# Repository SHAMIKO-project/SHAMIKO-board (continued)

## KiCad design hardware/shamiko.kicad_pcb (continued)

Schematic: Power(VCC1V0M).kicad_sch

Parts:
C27: 100u; CP_Elec_6.3x7.7; LCSC C48587228
C28, C35: 10u; C_0805_2012Metric; LCSC C440198
C29, C36: 330u; CP_Elec_6.3x7.7; LCSC C48587229
C30: 47u; C_0805_2012Metric; LCSC C124129
C31, C37: 0.01u; C_0603_1608Metric; LCSC C85973
C32: 0.1u; C_0603_1608Metric; LCSC C77055
C33: 2.2u; C_0805_2012Metric; LCSC C117966
C34: 4.7u; C_0805_2012Metric; LCSC C408144
C38: 1u; C_0603_1608Metric; LCSC C77386
C39: 1n; C_0603_1608Metric; LCSC C77026
IC1: LT3071; LT3071EUFD#PBF; LCSC C117304
J2, J3: SMA; SMA_Amphenol_132134-14_Vertical; LCSC C3174425
JP1: Jumper_2_Open; PinHeader_1x02_P2.54mm_Vertical; LCSC C42431798
R13: 0; R_2512_6332Metric_Pad1.40x3.35mm_HandSolder; LCSC C5204052
R14: 50k; R_0603_1608Metric; LCSC C861451
R15: 0; R_2512_6332Metric; LCSC C5204052; not fitted
R16: 100m; R_2512_6332Metric_Pad1.40x3.35mm_HandSolder; LCSC C840616
R17, R18: 0; R_1206_3216Metric; LCSC C137394
R19: 1k; R_0603_1608Metric; LCSC C22548
RV1: 10k; Potentiometer_Bourns_3296W_Vertical; LCSC C34846
TP1: TestPoint; TestPoint_Pad_D1.0mm; LCSC None; not fitted

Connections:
+1V0M: JP1.2 (B), R15.2, R16.2, R18.1, TP1.1; also elsewhere on the board
+1V0MB: R13.2, R15.1; also elsewhere on the board
+1V2: C29.1, C30.1, IC1.5 (IN_1), IC1.6 (IN_2), IC1.7 (IN_3), IC1.8 (IN_4), RV1.1; also elsewhere on the board
+3.3VP: C27.1, C28.1, IC1.27 (BIAS), IC1.28 (EN), R14.1; also elsewhere on the board
GND: C27.2, C28.2, C29.2, C30.2, C31.2, C32.2, C33.2, C34.2, C35.2, C36.2, C37.2, C38.2, C39.2, IC1.4 (GND_1), IC1.9 (GND_2), IC1.10 (GND_3), IC1.11 (GND_4), IC1.12 (GND_5), IC1.13 (GND_6), IC1.14 (GND_7), IC1.20 (GND_8), IC1.25 (VO2), IC1.26 (GND_9), IC1.29 (GND_10), J2.2 (Ext), J3.2 (Ext), R19.2, RV1.3; also elsewhere on the board
unnamed: IC1.21 (IMON), R19.1
unnamed: C38.1, IC1.22 (MARGA), RV1.2
unnamed: C31.1, C32.1, C33.1, C34.1, C35.1, C36.1, IC1.15 (OUT_1), IC1.16 (OUT_2), IC1.17 (OUT_3), IC1.18 (OUT_4), IC1.19 (SENSE), JP1.1 (A), R13.1, R16.1, R17.1
unnamed: IC1.2 (PWRGD), R14.2
unnamed: C37.1, IC1.3 (REF/BYP)
unnamed: C39.1, IC1.1 (VIOC)
unnamed: J2.1 (In), R17.2
unnamed: J3.1 (In), R18.2

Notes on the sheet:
NMT

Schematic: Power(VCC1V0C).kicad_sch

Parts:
C40, C42: 100u; CP_Elec_6.3x7.7; LCSC C48587228
C41, C43, C46: 10u; C_0805_2012Metric; LCSC C440198
C44: 2.2u; C_0603_1608Metric; LCSC C77047
C45: 4.7u; C_0603_1608Metric; LCSC C90057
C47: 330u; CP_Elec_6.3x7.7; LCSC C48587229
C48: 0.01u; C_0603_1608Metric; LCSC C85973
C49: 1u; C_0603_1608Metric; LCSC C77386
C50: 1n; C_0603_1608Metric; LCSC C77026
IC2: LT3071; LT3071EUFD#PBF; LCSC C117304
R20: 50k; R_0603_1608Metric; LCSC C861451
R21: 1k; R_0603_1608Metric; LCSC C22548
RV2: 10k; Potentiometer_Bourns_3296W_Vertical; LCSC C34846
TP2: TestPoint; TestPoint_Pad_D1.0mm; LCSC None; not fitted

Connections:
+1V0C: C44.1, C45.1, C46.1, C47.1, IC2.15 (OUT_1), IC2.16 (OUT_2), IC2.17 (OUT_3), IC2.18 (OUT_4), IC2.19 (SENSE), TP2.1; also elsewhere on the board
+1V2: C42.1, C43.1, IC2.5 (IN_1), IC2.6 (IN_2), IC2.7 (IN_3), IC2.8 (IN_4), RV2.1; also elsewhere on the board
+3.3VP: C40.1, C41.1, IC2.27 (BIAS), IC2.28 (EN), R20.1; also elsewhere on the board
GND: C40.2, C41.2, C42.2, C43.2, C44.2, C45.2, C46.2, C47.2, C48.2, C49.2, C50.2, IC2.4 (GND_1), IC2.9 (GND_2), IC2.10 (GND_3), IC2.11 (GND_4), IC2.12 (GND_5), IC2.13 (GND_6), IC2.14 (GND_7), IC2.20 (GND_8), IC2.25 (VO2), IC2.26 (GND_9), IC2.29 (GND_10), R21.2, RV2.3; also elsewhere on the board
unnamed: IC2.21 (IMON), R21.1
unnamed: C49.1, IC2.22 (MARGA), RV2.2
unnamed: IC2.2 (PWRGD), R20.2
unnamed: C48.1, IC2.3 (REF/BYP)
unnamed: C50.1, IC2.1 (VIOC)

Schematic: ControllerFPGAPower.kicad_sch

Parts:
C146, C153, C160, C167, C173, C187: 47u; C_0805_2012Metric; LCSC C124129
C147, C148, C154, C155, C161, C162, C168, C169, C170, C174, C175, C182, C183, C188: 4.7u; C_0603_1608Metric; LCSC C90057
C149, C150, C151, C152, C156, C157, C158, C159, C163, C164, C165, C166, C171, C172, C176, C177, C178, C179, C180, C184, C185, C186, C189: 0.47u; C_0402_1005Metric; LCSC C77003
C181: 0.01u; C_0402_1005Metric; LCSC C15195
FB3, FB4: MMZ1005S601CT000; LCSC C76804
U5: XC7S25-1CSGA225C; LCSC C1521699

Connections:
+1V0C: C182.1, C183.1, C184.1, C185.1, C186.1, C187.1, C188.1, C189.1, U5.E8 (VCCINT_1), U5.E10 (VCCINT_2), U5.F7 (VCCINT_3), U5.G6 (VCCBRAM_1), U5.G10 (VCCINT_4), U5.H7 (VCCINT_5), U5.J6 (VCCBRAM_2), U5.J10 (VCCINT_6), U5.K7 (VCCINT_7), U5.K9 (VCCINT_8); also elsewhere on the board
+1V8: C167.1, C168.1, C169.1, C170.1, C171.1, C172.1, FB3.1, U5.L6 (VCCAUX_1), U5.L8 (VCCAUX_2); also elsewhere on the board
+3V3C: C146.1, C147.1, C148.1, C149.1, C150.1, C151.1, C152.1, C153.1, C154.1, C155.1, C156.1, C157.1, C158.1, C159.1, C160.1, C161.1, C162.1, C163.1, C164.1, C165.1, C166.1, C173.1, C174.1, C175.1, C176.1, C177.1, C178.1, C179.1, U5.B7 (VCCO_15_1), U5.C3 (VCCO_34_1), U5.C11 (VCCO_15_2), U5.E6 (VCCO_0_1), U5.F12 (VCCO_15_3), U5.G2 (VCCO_34_2), U5.H5 (CFGBVS_0), U5.J14 (VCCO_14_1), U5.L3 (VCCO_34_3), U5.M12 (VCCO_14_2), U5.P5 (VCCO_0_2), U5.P9 (VCCO_14_3); also elsewhere on the board
GND: C146.2, C147.2, C148.2, C149.2, C150.2, C151.2, C152.2, C153.2, C154.2, C155.2, C156.2, C157.2, C158.2, C159.2, C160.2, C161.2, C162.2, C163.2, C164.2, C165.2, C166.2, C167.2, C168.2, C169.2, C170.2, C171.2, C172.2, C173.2, C174.2, C175.2, C176.2, C177.2, C178.2, C179.2, C180.2, C182.2, C183.2, C184.2, C185.2, C186.2, C187.2, C188.2, C189.2, FB4.1, U5.A1 (GND_1), U5.A15 (GND_2), U5.B8 (GND_3), U5.C2 (GND_4), U5.C12 (GND_5), U5.D5 (VCCBATT_0), U5.D6 (GND_6), U5.D14 (GND_7), U5.E4 (GND_8), U5.E7 (GND_9), U5.E9 (GND_10), U5.F6 (GND_11), U5.F10 (GND_12), U5.F13 (GND_13), U5.G3 (GND_14), U5.G7 (GND_15), U5.H6 (GND_16), U5.H10 (GND_17), U5.J7 (GND_18), U5.J8 (DXN_0), U5.J9 (DXP_0), U5.J13 (GND_19), U5.K6 (GND_20), U5.K8 (GND_21), U5.K10 (GND_22), U5.L2 (GND_23), U5.L7 (GND_24), U5.L9 (GND_25), U5.M11 (GND_26), U5.P4 (GND_27), U5.P8 (GND_28), U5.P13 (GND_29), U5.R1 (GND_30), U5.R15 (GND_31); also elsewhere on the board
unnamed: C181.2, FB4.2, U5.F8 (GNDADC_0), U5.G8 (VREFN_0), U5.G9 (VP_0), U5.H8 (VN_0), U5.H9 (VREFP_0)
unnamed: C180.1, C181.1, FB3.2, U5.F9 (VCCADC_0)

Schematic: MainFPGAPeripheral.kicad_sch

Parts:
D8, D9, D10, D11, D12, D13, D14, D15: R_LED; LED_0603_1608Metric; LCSC C965798
R65, R66, R67, R68, R69, R70, R71, R72: 200; R_0603_1608Metric; LCSC C2907123
RN1, RN2, RN3: 4.7k; YAGEO_R_network; LCSC C327044
SW3, SW4, SW5, SW6: SW_MEC_5E; MySW_PUSH_6mm_H5mm; LCSC C393938
SW7: SW_DIP_x08; SW_DIP_SPSTx08_Slide_9.78x22.5mm_W8.61mm_P2.54mm; LCSC C2842674

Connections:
+3V3M: R65.1, R66.1, R67.1, R68.1, R69.1, R70.1, R71.1, R72.1, SW3.3 (K), SW3.4 (A), SW4.3 (K), SW4.4 (A), SW5.3 (K), SW5.4 (A), SW6.3 (K), SW6.4 (A), SW7.9, SW7.10, SW7.11, SW7.12, SW7.13, SW7.14, SW7.15, SW7.16; also elsewhere on the board
GND: RN1.1, RN1.2, RN1.3, RN1.4, RN2.1, RN2.2, RN2.3, RN2.4, RN3.1, RN3.2, RN3.3, RN3.4; also elsewhere on the board
M_DIPSW_0: RN3.5, SW7.8; also elsewhere on the board
M_DIPSW_1: RN3.6, SW7.7; also elsewhere on the board
M_DIPSW_2: RN3.7, SW7.6; also elsewhere on the board
M_DIPSW_3: RN3.8, SW7.5; also elsewhere on the board
M_DIPSW_4: RN2.5, SW7.4; also elsewhere on the board
M_DIPSW_5: RN2.6, SW7.3; also elsewhere on the board
M_DIPSW_6: RN2.7, SW7.2; also elsewhere on the board
M_DIPSW_7: RN2.8, SW7.1; also elsewhere on the board
M_LED_0: D8.1 (K); also elsewhere on the board
M_LED_1: D9.1 (K); also elsewhere on the board
M_LED_2: D10.1 (K); also elsewhere on the board
M_LED_3: D11.1 (K); also elsewhere on the board
M_LED_4: D12.1 (K); also elsewhere on the board
M_LED_5: D13.1 (K); also elsewhere on the board
M_LED_6: D14.1 (K); also elsewhere on the board
M_LED_7: D15.1 (K); also elsewhere on the board
M_TACTSW_0: RN1.5, SW6.1, SW6.2; also elsewhere on the board
M_TACTSW_1: RN1.6, SW5.1, SW5.2; also elsewhere on the board
M_TACTSW_2: RN1.7, SW4.1, SW4.2; also elsewhere on the board
M_TACTSW_3: RN1.8, SW3.1, SW3.2; also elsewhere on the board
unnamed: D8.2 (A), R65.2
unnamed: D9.2 (A), R66.2
unnamed: D10.2 (A), R67.2
unnamed: D11.2 (A), R68.2
unnamed: D12.2 (A), R69.2
unnamed: D13.2 (A), R70.2
unnamed: D14.2 (A), R71.2
unnamed: D15.2 (A), R72.2

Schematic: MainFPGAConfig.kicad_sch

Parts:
C190, C191, C192: 0.1u; C_0603_1608Metric; LCSC C77055
D2: B_LED; LED_0603_1608Metric; LCSC C19171394
D3, D4: G_LED; LED_0603_1608Metric; LCSC C5342733
J4: JTAG_CONFIG; JTAG_2x7_P2.54mm; LCSC C240854
R31, R32, R33, R40, R41, R43, R44, R45: 4.7k; R_0603_1608Metric; LCSC C99782
R34, R35, R36, R47: 1k; R_0603_1608Metric; LCSC C22548
R37, R38, R39: 200; R_0603_1608Metric; LCSC C2907123
R42: 2.4k; R_0603_1608Metric; LCSC C22940
R46: 330; R_0603_1608Metric; LCSC C105881
SW1: SW_DIP_x03; SW_DIP_SPSTx03_Slide_9.78x9.8mm_W8.61mm_P2.54mm; LCSC C3012353
U4: XC7S100-2FGGA484I; Xilinx_FBG484; LCSC C1521770
U6: IS25LP064A-JLLE; WSON-8-1EP_8x6mm_P1.27mm_EP3.4x4.3mm; LCSC C1349830
U7, U8: SN74LVC2G17DCKRE4; LCSC C50714

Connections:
+3V3M: C190.1, C191.1, C192.1, D3.2 (A), D4.2 (A), J4.2, R31.1, R32.1, R33.1, R40.1, R41.1, R42.1, R43.1, R44.1, R45.1, R46.1, SW1.1, SW1.2, SW1.3, U6.8 (VCC), U7.5 (VCC), U8.5 (VCC); also elsewhere on the board
/Main FPGA Configuration/MX_JTAG_TCK: U4.G9 (TCK_0), U7.4 (2Y)
/Main FPGA Configuration/MX_JTAG_TDI: U4.W9 (TDI_0), U8.4 (2Y)
/Main FPGA Configuration/MX_JTAG_TDO: R43.2, U4.W10 (TDO_0), U8.1 (1A)
/Main FPGA Configuration/MX_JTAG_TMS: U4.Y10 (TMS_0), U7.6 (1Y)
/Main FPGA Configuration/M_CONFIG_M0: R34.1, SW1.6, U4.T11 (M0_0)
/Main FPGA Configuration/M_CONFIG_M1: R35.1, SW1.5, U4.T10 (M1_0)
/Main FPGA Configuration/M_CONFIG_M2: R36.1, SW1.4, U4.U10 (M2_0)
/Main FPGA Configuration/M_JTAG_TCK: J4.6, R32.2, U7.3 (2A)
/Main FPGA Configuration/M_JTAG_TDI: J4.10, R33.2, U8.3 (2A)
/Main FPGA Configuration/M_JTAG_TDO: J4.8, U8.6 (1Y)
/Main FPGA Configuration/M_JTAG_TMS: J4.4, R31.2, U7.1 (1A)
/Main FPGA Configuration/M_S_CLOCK: U4.D9 (CCLK_0), U6.6 (SCK)
/Main FPGA Configuration/M_S_D0: U4.M21 (IO_L1P_T0_D00_MOSI_14), U6.5 (SI_(IO0))
/Main FPGA Configuration/M_S_D1: U4.M22 (IO_L1N_T0_D01_DIN_14), U6.2 (SO_(IO1))
/Main FPGA Configuration/M_S_D2: R41.2, U4.N21 (IO_L2P_T0_D02_14), U6.3 (WP#_(IO2))
/Main FPGA Configuration/M_S_D3: R40.2, U4.N22 (IO_L2N_T0_D03_14), U6.7 (HOLD#_(IO3))
/Main FPGA Configuration/M_S_SELECTn: R42.2, U4.N17 (IO_L6P_T0_FCS_B_14), U6.1 (CE#)
GND: C190.2, C191.2, C192.2, J4.1, J4.3, J4.5, J4.7, J4.9, J4.11, J4.13, R34.2, R35.2, R36.2, R37.2, R47.2, U6.4 (GND), U6.9 (EPAD), U7.2 (GND), U8.2 (GND); also elsewhere on the board
M_DONE: D2.2 (A), R46.2, U4.U9 (DONE_0); also elsewhere on the board
M_INIT_B: R38.2, R45.2, U4.T9 (INIT_B_0)
M_PROG_B: R39.2, R44.2, U4.U11 (PROGRAM_B_0); also elsewhere on the board
unnamed: D2.1 (K), R37.1
unnamed: D3.1 (K), R38.1
unnamed: D4.1 (K), R39.1
unnamed: R47.1, U4.M19 (IO_L3P_T0_DQS_PUDC_B_14)

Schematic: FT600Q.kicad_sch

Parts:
C223, C224, C225, C226, C228, C231, C232, C233, C234, C235, C236, C237, C239, C240, C241, C242: 0.1u; C_0603_1608Metric; LCSC C77055
C227: 100u; CP_Elec_6.3x7.7; LCSC C48587228
C229: 10u; C_0805_2012Metric; LCSC C440198
C230: 1u; NFM31HK103R1H3L; LCSC C92518
C238: 4.7u; C_0603_1608Metric; LCSC C90057
C243, C244: 18p; C_0603_1608Metric; LCSC C1647
FB9, FB10, FB11, FB12, FB13: BLM18PG221SN1D; BLM18SP221SN1B; LCSC C80165
FL2, FL3, FL4: DLM0NSN500HY2D; LCSC C1857796
J8: 692221030100; LCSC C5334230
R93: 4.7k; R_0603_1608Metric; LCSC C99782
R94: 10k; R_0603_1608Metric; LCSC C95204
R95: 1.6k; R_0603_1608Metric; LCSC C22847
U14: LM2937IMP-3.3; SOT-223; LCSC C140265
U15, U17, U18: TPD2EUSB30; Texas_DRT-3; LCSC C97502
U16: FT600; QFN-56-1EP_7x7mm_P0.4mm_EP4x4mm; LCSC C5252722
Y2: 30MHz; Crystal_SMD_5032-2Pin_5.0x3.2mm; LCSC C19272757

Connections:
+5V: C228.1, U14.1 (VI); also elsewhere on the board
/FT600Q/FT600_D+: FL2.1, J8.3 (D+), U15.1 (D+)
/FT600Q/FT600_D-: FL2.4, J8.2 (D-), U15.2 (D-)
/FT600Q/RID+: FL4.3, U16.28 (RIDP)
/FT600Q/RID-: FL4.2, U16.27 (RIDN)
/FT600Q/SSRX+: FL4.4, J8.9 (SSRX+), U18.1 (D+)
/FT600Q/SSRX-: FL4.1, J8.8 (SSRX-), U18.2 (D-)
/FT600Q/SSTX+: FL3.4, J8.6 (SSTX+), U17.1 (D+)
/FT600Q/SSTX-: FL3.1, J8.5 (SSTX-), U17.2 (D-)
/FT600Q/TI_C_D+: C237.1, FL3.3
/FT600Q/TI_C_D-: C236.1, FL3.2
/FT600Q/TODN: C236.2, U16.24 (TODN)
/FT600Q/TODP: C237.2, U16.25 (TODP)
/FT600Q/USB3_D+: FL2.2, U16.18 (DP)
/FT600Q/USB3_D-: FL2.3, U16.20 (DM)
/FT600Q/VD10: C238.1, C239.1, C240.1, C241.1, C242.1, U16.1 (AVDD), U16.23 (VD10), U16.26 (VD10), U16.31 (DV10), U16.37 (VD10), U16.50 (VD10)
C_RST: U16.10 (~RESET); also elsewhere on the board
FT600_BE0: U16.2 (BE_0); also elsewhere on the board
FT600_BE1: U16.3 (BE_1); also elsewhere on the board
FT600_CLK: U16.43 (CLK); also elsewhere on the board
FT600_DATA_0: U16.33 (DATA_0); also elsewhere on the board
FT600_DATA_1: U16.34 (DATA_1); also elsewhere on the board
FT600_DATA_2: U16.35 (DATA_2); also elsewhere on the board
FT600_DATA_3: U16.36 (DATA_3); also elsewhere on the board
FT600_DATA_4: U16.39 (DATA_4); also elsewhere on the board
FT600_DATA_5: U16.40 (DATA_5); also elsewhere on the board
FT600_DATA_6: U16.41 (DATA_6); also elsewhere on the board
FT600_DATA_7: U16.42 (DATA_7); also elsewhere on the board
FT600_DATA_8: U16.45 (DATA_8); also elsewhere on the board
FT600_DATA_9: U16.46 (DATA_9); also elsewhere on the board
FT600_DATA_10: U16.47 (DATA_10); also elsewhere on the board
FT600_DATA_11: U16.48 (DATA_11); also elsewhere on the board
FT600_DATA_12: U16.53 (DATA_12); also elsewhere on the board
FT600_DATA_13: U16.54 (DATA_13); also elsewhere on the board
FT600_DATA_14: U16.55 (DATA_14); also elsewhere on the board
FT600_DATA_15: U16.56 (DATA_15); also elsewhere on the board
FT600_GPIO0: U16.12 (GPIO0); also elsewhere on the board
FT600_GPIO1: U16.13 (GPIO1); also elsewhere on the board
FT600_OE: U16.9 (~OE); also elsewhere on the board
FT600_RD: U16.8 (~RD); also elsewhere on the board
FT600_RXF: U16.5 (~RXF); also elsewhere on the board
FT600_SIWU: U16.6 (~SIWU); also elsewhere on the board
FT600_TXE: U16.4 (~TXE); also elsewhere on the board
FT600_WAKEUP: U16.11 (~WAKEUP); also elsewhere on the board
FT600_WR: U16.7 (~WR); also elsewhere on the board
GND: C223.2, C224.2, C225.2, C226.2, C227.2, C228.2, C229.2, C230.2, C231.2, C232.2, C233.2, C234.2, C235.2, C238.2, C239.2, C240.2, C241.2, C242.2, C243.1, C244.1, FB11.1, FB12.1, FB13.1, R94.2, R95.2, U14.2 (GND), U14.4 (GND), U15.3 (GND), U16.32 (GND), U16.49 (GND), U16.51 (GND), U16.57 (GND), U17.3 (GND), U18.3 (GND); also elsewhere on the board
unnamed: C223.1, C224.1, C225.1, C226.1, C227.1, FB9.2, U16.38 (VCCIO), U16.44 (VCCIO), U16.52 (VCCIO)
unnamed: C230.1, FB10.2
unnamed: FB11.2, J8.10 (SHIELD), J8.11 (SHIELD)
unnamed: FB12.2, J8.7 (DRAIN)
unnamed: FB13.2, J8.4 (GND)
unnamed: C229.1, FB9.1, FB10.1, U14.3 (VO)
unnamed: R95.1, U16.21 (RREF)
unnamed: R93.2, R94.1, U16.29 (VBUS)
unnamed: C230.3, C231.1, C232.1, C233.1, C234.1, U16.15 (VCC33), U16.19 (VCC33), U16.22 (VDDA), U16.30 (VCC33)
unnamed: C244.2, U16.16 (XI), Y2.1
unnamed: C243.2, U16.17 (XO), Y2.2
VBUS_FT600: C235.1, J8.1 (VBUS), R93.1

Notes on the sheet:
FT600 2.5V Power Line

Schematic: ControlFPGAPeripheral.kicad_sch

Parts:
D16, D17, D18, D19, D20, D21, D22, D23: R_LED; LED_0603_1608Metric; LCSC C965798
R73, R74, R75, R76, R77, R78, R79, R80: 200; R_0603_1608Metric; LCSC C2907123
R81, R82: 4.7k; R_0603_1608Metric; LCSC C99782
RN4, RN5: 4.7k; YAGEO_R_network; LCSC C327044
SW8, SW9: SW_MEC_5E; MySW_PUSH_6mm_H5mm; LCSC C393938
SW10: SW_DIP_x08; SW_DIP_SPSTx08_Slide_9.78x22.5mm_W8.61mm_P2.54mm; LCSC C2842674

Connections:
+3V3C: R73.1, R74.1, R75.1, R76.1, R77.1, R78.1, R79.1, R80.1, SW8.3 (K), SW8.4 (A), SW9.3 (K), SW9.4 (A), SW10.9, SW10.10, SW10.11, SW10.12, SW10.13, SW10.14, SW10.15, SW10.16; also elsewhere on the board
C_DIPSW_0: RN4.8, SW10.1; also elsewhere on the board
C_DIPSW_1: RN4.7, SW10.2; also elsewhere on the board
C_DIPSW_2: RN4.6, SW10.3; also elsewhere on the board
C_DIPSW_3: RN4.5, SW10.4; also elsewhere on the board
C_DIPSW_4: RN5.8, SW10.5; also elsewhere on the board
C_DIPSW_5: RN5.7, SW10.6; also elsewhere on the board
C_DIPSW_6: RN5.6, SW10.7; also elsewhere on the board
C_DIPSW_7: RN5.5, SW10.8; also elsewhere on the board
C_LED_0: D16.1 (K); also elsewhere on the board
C_LED_1: D17.1 (K); also elsewhere on the board
C_LED_2: D18.1 (K); also elsewhere on the board
C_LED_3: D19.1 (K); also elsewhere on the board
C_LED_4: D20.1 (K); also elsewhere on the board
C_LED_5: D21.1 (K); also elsewhere on the board
C_LED_6: D22.1 (K); also elsewhere on the board
C_LED_7: D23.1 (K); also elsewhere on the board
C_TACTSW_0: R81.1, SW8.1, SW8.2; also elsewhere on the board
C_TACTSW_1: R82.1, SW9.1, SW9.2; also elsewhere on the board
GND: R81.2, R82.2, RN4.1, RN4.2, RN4.3, RN4.4, RN5.1, RN5.2, RN5.3, RN5.4; also elsewhere on the board
unnamed: D16.2 (A), R73.2
unnamed: D17.2 (A), R74.2
unnamed: D18.2 (A), R75.2
unnamed: D19.2 (A), R76.2
unnamed: D20.2 (A), R77.2
unnamed: D21.2 (A), R78.2
unnamed: D22.2 (A), R79.2
unnamed: D23.2 (A), R80.2

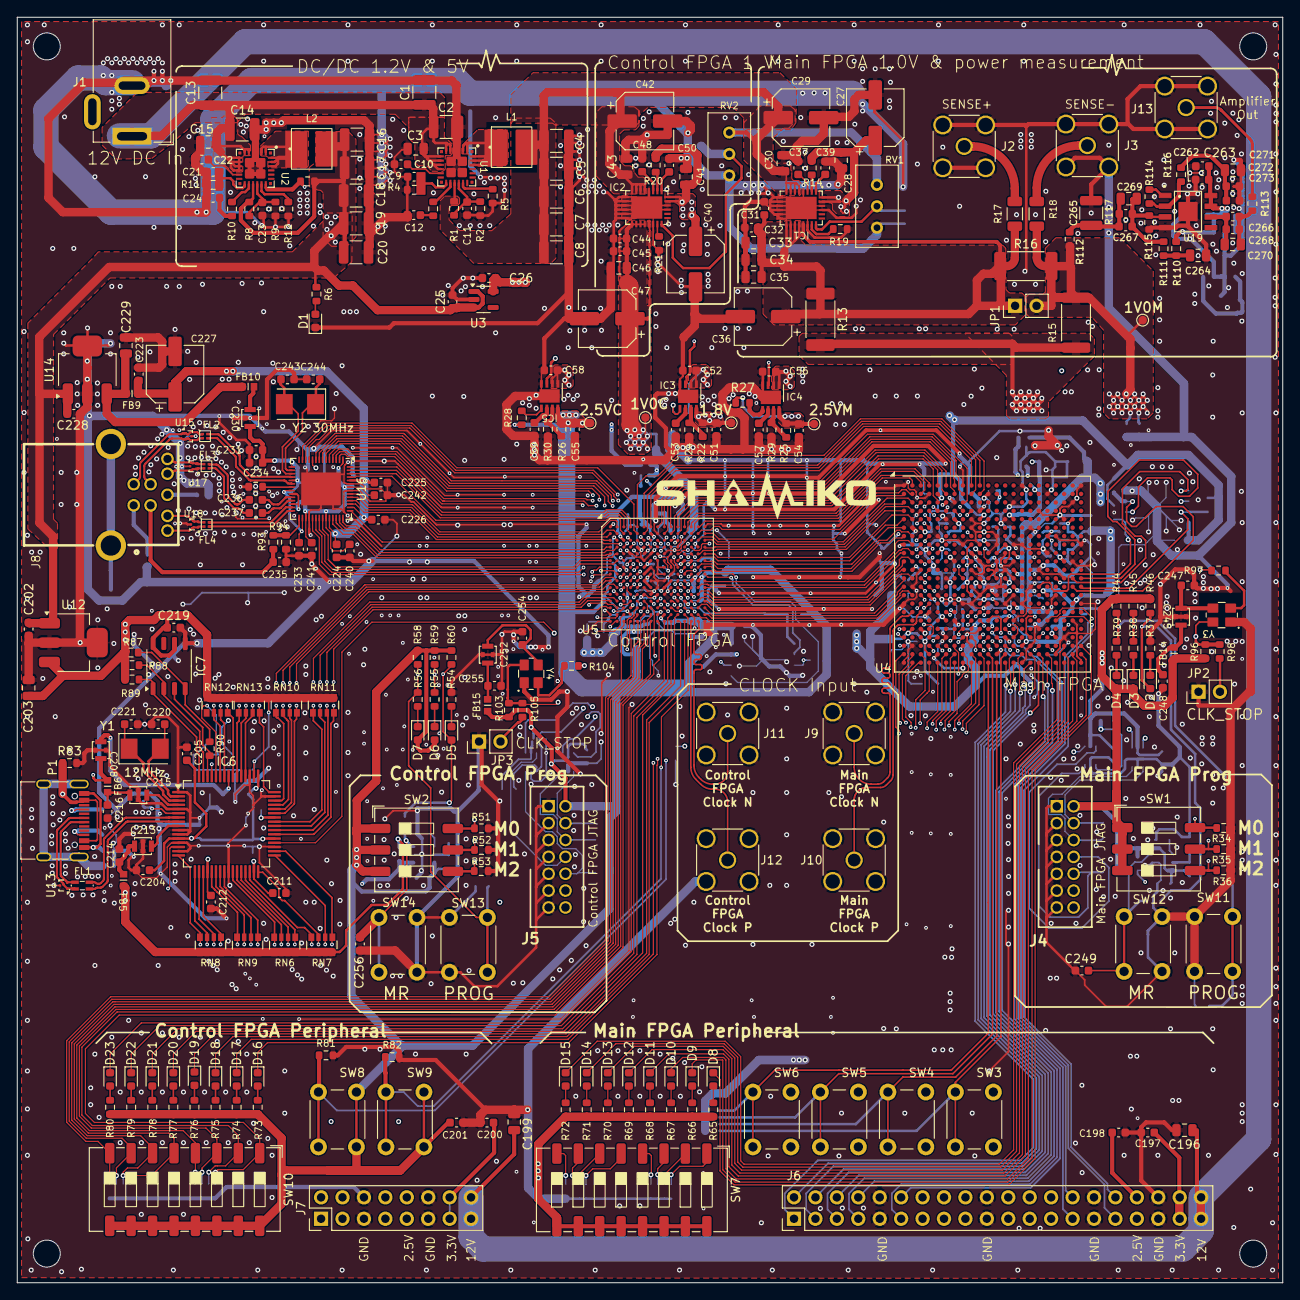
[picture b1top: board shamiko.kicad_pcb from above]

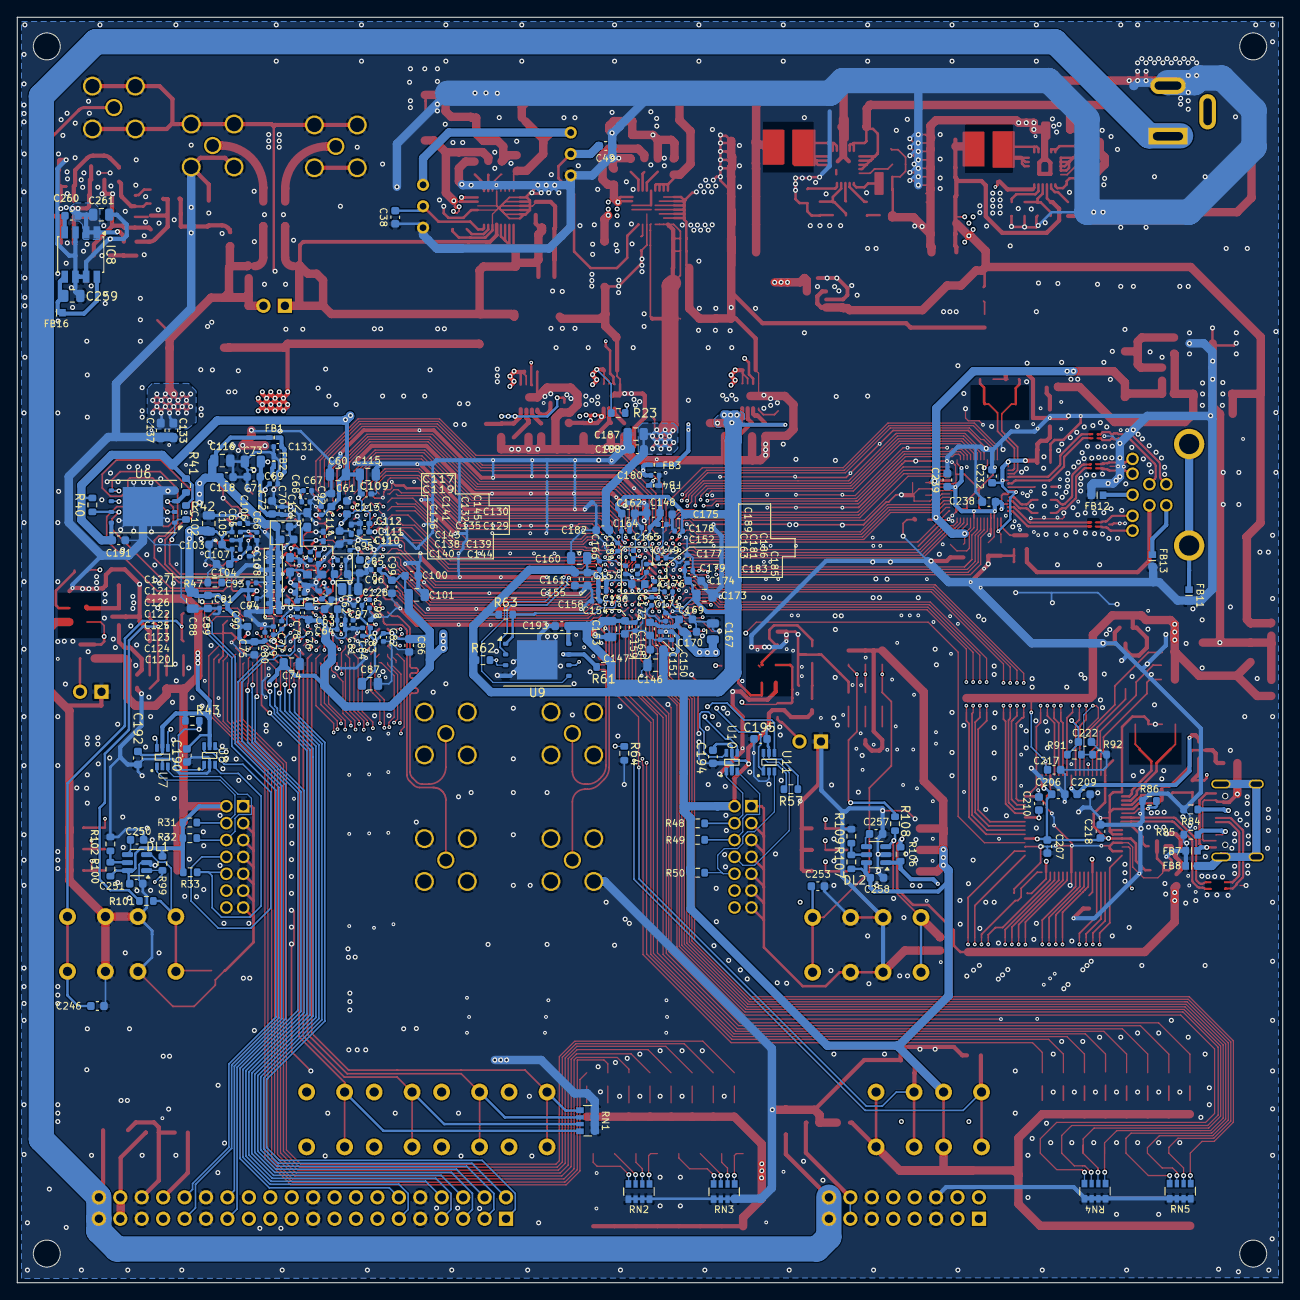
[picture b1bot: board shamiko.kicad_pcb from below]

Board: 6 copper layers, 150.0 x 150.0 mm, 523 parts (211 on the bottom side), 404 nets.
